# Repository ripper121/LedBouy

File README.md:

# LedBouy
This Led Bouy is for fishing or geocaching.
- falshes every 2 Sec for 250ms.
- will only flash if the LDR detects darkness (runntime not tested should be over a month with 18650 3400mA Battery)
- designed for LiPo battery 3-4.4V
- cuttoff voltage at 3.0V for unprotected LiPo´s
- best use with 18650 3400mA Battery, so the runntime is > 1 week when the LDR is disabled (flashes 24/7)

Code only compiles with Arduino 1.0.6 the new >1.6 throws errors!

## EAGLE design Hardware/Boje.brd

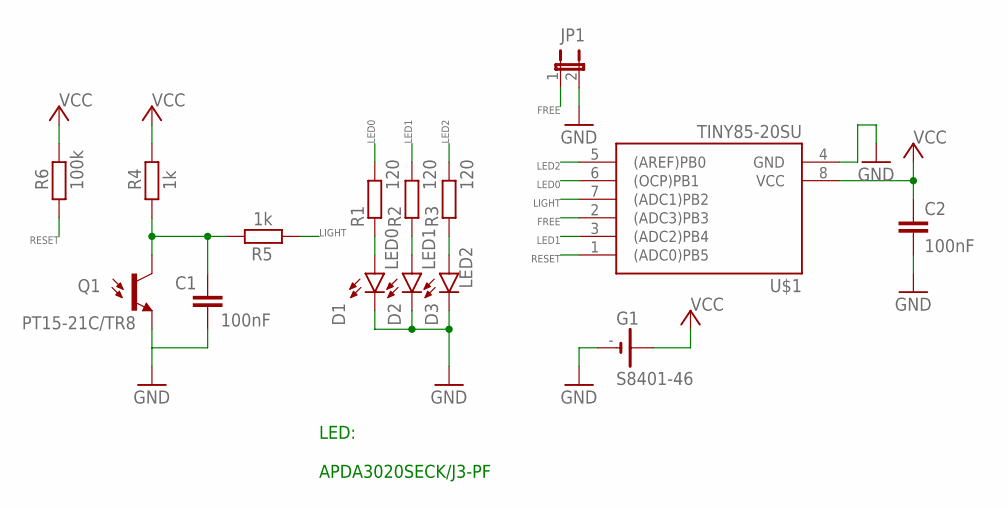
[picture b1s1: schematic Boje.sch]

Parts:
C1, C2: 100nF; C0603
D1: LED0; LED5MM
D2: LED1; LED5MM
D3: LED2; LED5MM
G1: S8401-46; CR2032V
JP1: JP1E; JP1
Q1: PT15-21C/TR8; PT17-21C-L41-TR8
R1, R2, R3: 120; R0603
R4, R5: 1k; R0603
R6: 100k; R0603
U$1: TINY85-20SU; SOIC8

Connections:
FREE: JP1.1, U$1.2 ((ADC3)PB3)
GND: C1.1, C2.2, D1.K (C), D2.K (C), D3.K (C), G1.-, JP1.2, Q1.E, U$1.4 (GND)
LED0: R1.2, U$1.6 ((OCP)PB1)
LED1: R2.2, U$1.3 ((ADC2)PB4)
LED2: R3.2, U$1.5 ((AREF)PB0)
LIGHT: R5.1, U$1.7 ((ADC1)PB2)
unnamed: C1.2, Q1.C, R4.1, R5.2
unnamed: D1.A, R1.1
unnamed: D2.A, R2.1
unnamed: D3.A, R3.1
RESET: R6.1, U$1.1 ((ADC0)PB5)
VCC: C2.1, G1.+0 (+), G1.+1 (+), R4.2, R6.2, U$1.8 (VCC)

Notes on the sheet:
LED: APDA3020SECK/J3-PF

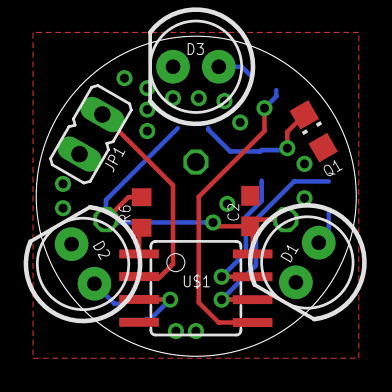
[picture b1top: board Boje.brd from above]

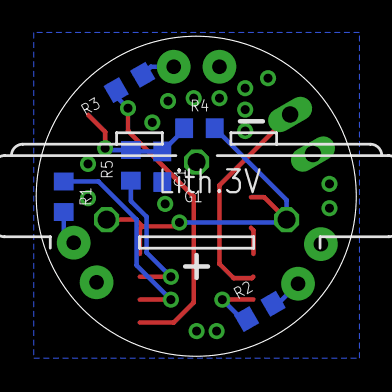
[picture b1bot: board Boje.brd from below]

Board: 2 copper layers, 17.8 x 17.8 mm, 15 parts (7 on the bottom side), 12 nets.

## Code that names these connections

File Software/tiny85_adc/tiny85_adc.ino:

// set timer to 0.016s
// WDTCR |= (0<<WDP3) | (0<<WDP2) | (0<<WDP1) | (0<<WDP0);
// set timer to 0.032s
// WDTCR |= (0<<WDP3) | (0<<WDP2) | (0<<WDP1) | (1<<WDP0);
// set timer to 0.064s
// WDTCR |= (0<<WDP3) | (0<<WDP2) | (1<<WDP1) | (0<<WDP0);
// set timer to 0.125s
// WDTCR |= (0<<WDP3) | (0<<WDP2) | (1<<WDP1) | (1<<WDP0);
// set timer to 0.250s
// WDTCR |= (0<<WDP3) | (1<<WDP2) | (0<<WDP1) | (0<<WDP0);
// set timer to 0.5s
// WDTCR |= (0<<WDP3) | (1<<WDP2) | (0<<WDP1) | (1<<WDP0);
//set timer to 1 sec
//WDTCR |= (0 << WDP3) | (1 << WDP2) | (1 << WDP1) | (0 << WDP0);
//set timer to 2 sec
//WDTCR |= (0<<WDP3) | (1<<WDP2) | (1<<WDP1) | (1<<WDP0);
//set timer to 4 sec
//WDTCR |= (1<<WDP3) | (0<<WDP2) | (0<<WDP1) | (0<<WDP0);
//set timer to 8 sec
//WDTCR |= (1<<WDP3) | (0<<WDP2) | (0<<WDP1) | (0<<WDP1);
#include <avr/interrupt.h>
#include <avr/sleep.h>
#include <avr/power.h>
#define DARKVAL 200
#define DEVIATION 1
#define HYST 6
byte power_counter = 1;
int adc_in = 1023;
int adc_in_pref = 1023;
int adc_dev = 1023;
int addr = 0;
ISR(WDT_vect) {
  power_counter--;
}

void setup() {
  // set timer to 0.5s
  WDTCR |= (0 << WDP3) | (1 << WDP2) | (0 << WDP1) | (1 << WDP0) | (1 << WDIE) | (0 << WDE);
  set_sleep_mode(SLEEP_MODE_PWR_DOWN);
}

void loop() {
  //-----POWER OFF START-----
  //PortB Input LOW
  DDRB = 0x00;
  PORTB = 0x00;
  power_all_disable();
  //Go Sleep
  sleep_enable();
  sleep_mode();
  sleep_disable();
  //-----POWER OFF END  -----

  //-----READ ADC START-----
  //Save old value
  adc_in_pref = adc_in;
  //PB2 Input Pullup
  DDRB &= ~(1 << DDB2);
  PORTB |= (1 << PB2);
  power_adc_enable();
  // Set the ADC input to PB2/ADC1
  ADMUX |= (1 << MUX0) | (1 << ADLAR);
  // Set the prescaler to clock/128 & enable ADC
  ADCSRA |= (1 << ADPS1) | (1 << ADPS0) | (1 << ADEN) | (1 << ADSC);
  // Wait for it to finish
  while (ADCSRA & (1 << ADSC));
  //adc_in = (ADCH << 8) | ADCL;
  adc_in = ADCH;
  //Turn off ADC
  ACSR |= _BV(ACD);                         //disable the analog comparator
  ADCSRA &= ~_BV(ADEN);                     //disable ADC
  power_adc_disable();
  //-----READ ADC END  -----
  if (power_counter < 1 | power_counter > HYST) {
    power_counter = 1;
    //Get DEVIATION
    if (adc_in > adc_in_pref)
      adc_dev = adc_in - adc_in_pref;
    else
      adc_dev = adc_in_pref - adc_in;

    //Check DEVIATION and DARKVAL
    if (adc_dev > DEVIATION && adc_in > DARKVAL) {
      DDRB |= (1 << DDB0) | (1 << DDB1) | (1 << DDB4);
      for (byte i = 0; i < 10; i++) {
        PORTB ^= (1 << PB0) | (1 << PB1) | (1 << PB4);
        _delay_ms(100);
      }
      power_counter = HYST;
    }
  }
}

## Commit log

2015-12-17 First Version
2015-12-17 Update Arduino 1.6 Issue
2015-12-17 Runntime Calculator
2016-01-06 Board Update
2016-01-06 Part Change
2016-01-08 New Layout
2016-01-11 Gerber
2016-01-11 Costs
2016-05-31 New PCB Layout
2016-05-31 update code
2016-06-01 reactive light
2016-06-01 add hysterese
2016-06-01 optim.
2016-06-02 ADCTestVal
2016-09-16 latest

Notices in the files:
parts and their libraries:
SparkFun-LED: Licensing: Creative Commons ShareAlike 4.0 International - https://creativecommons.org/licenses/by-sa/4.0
